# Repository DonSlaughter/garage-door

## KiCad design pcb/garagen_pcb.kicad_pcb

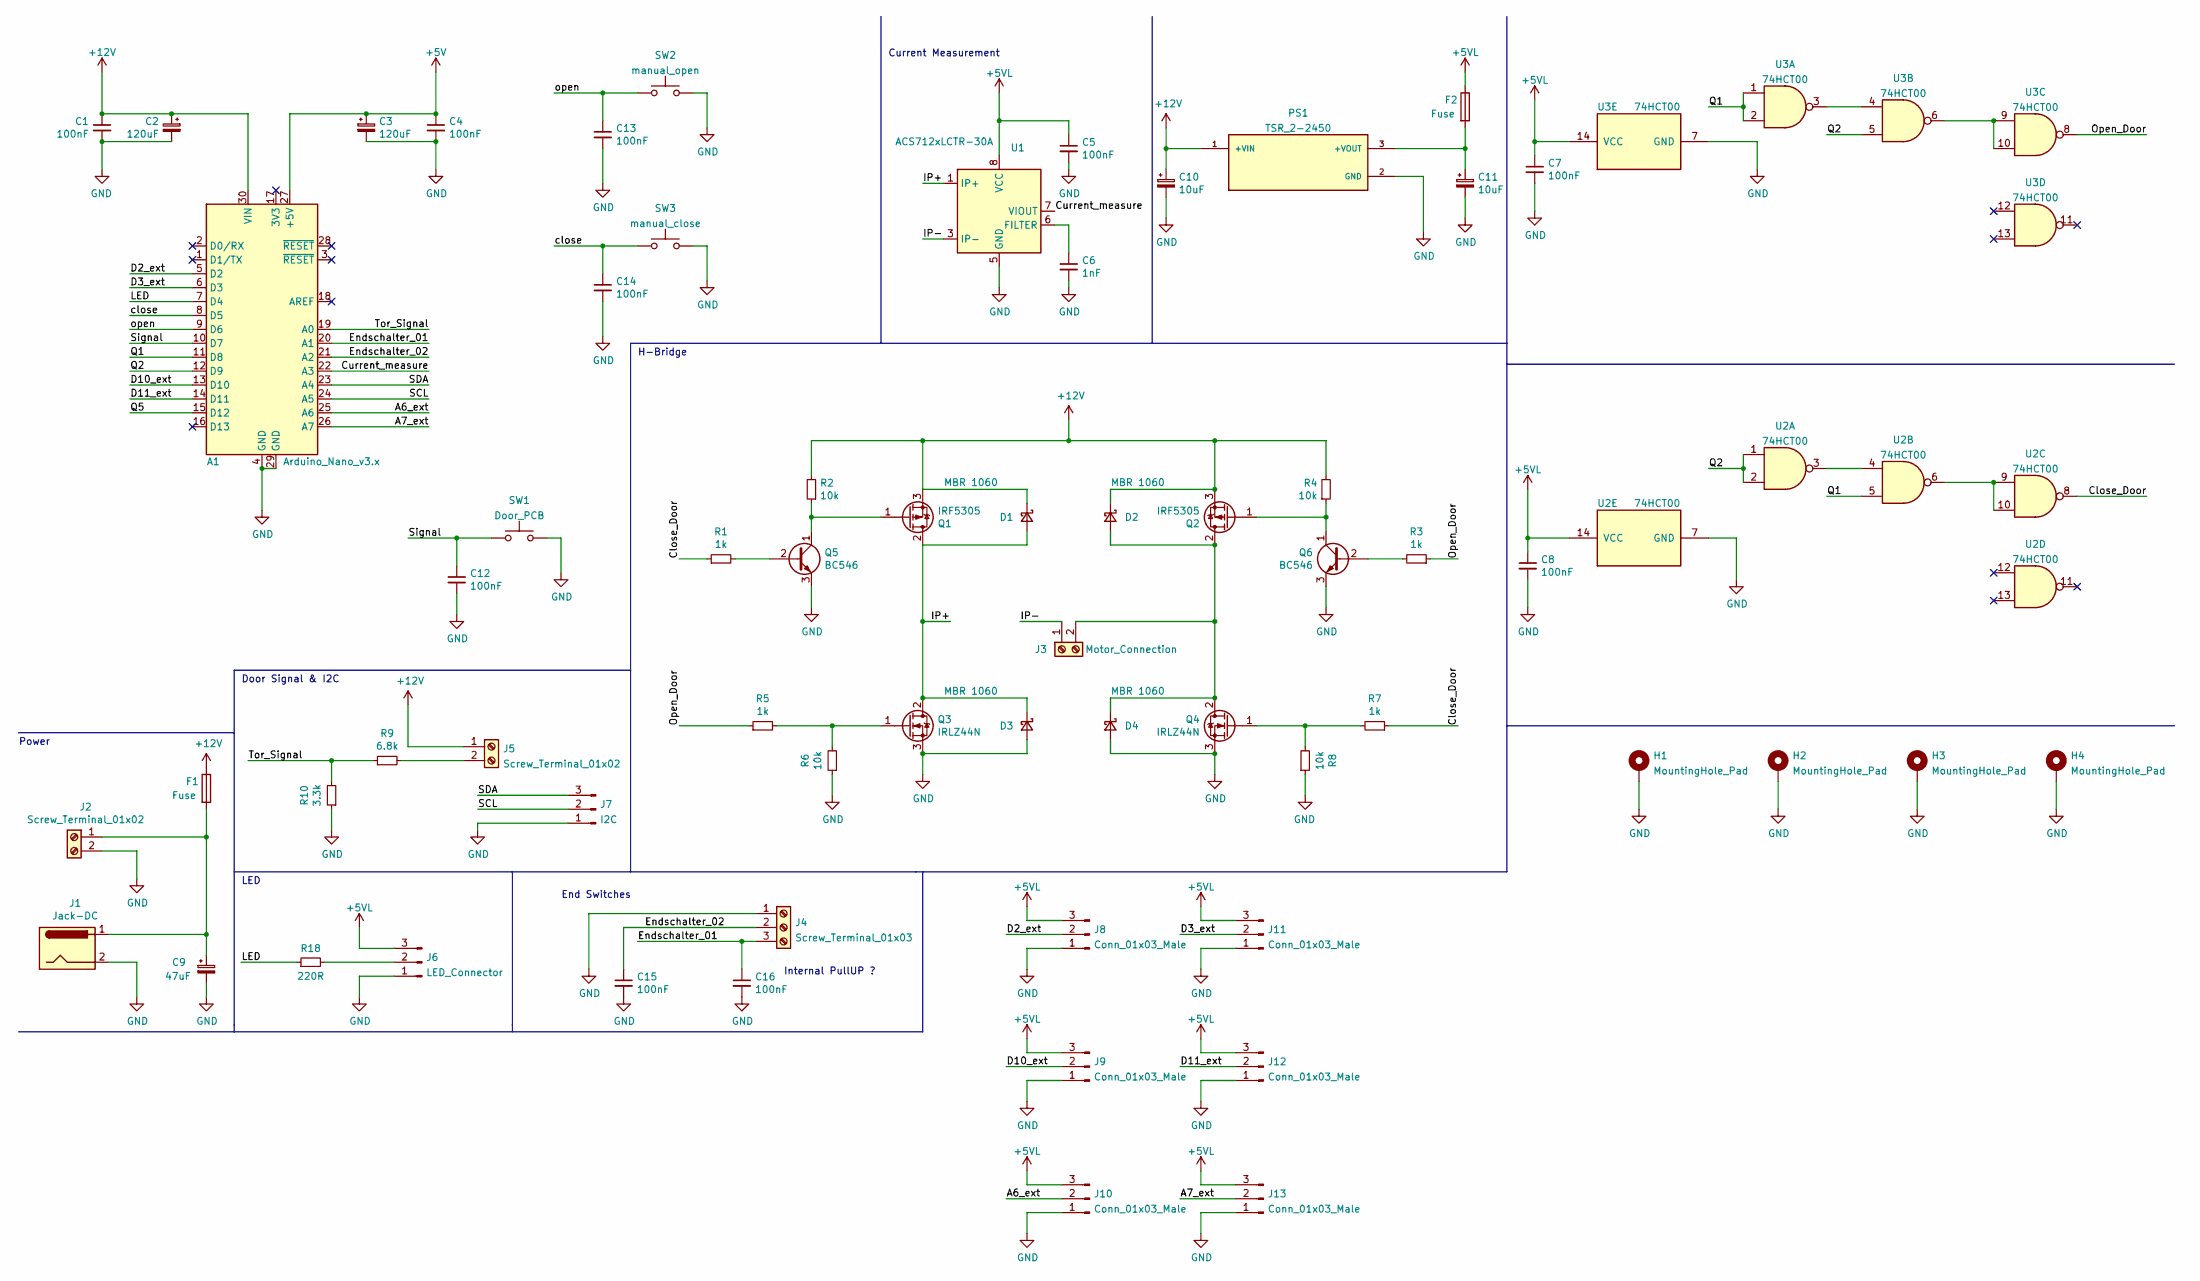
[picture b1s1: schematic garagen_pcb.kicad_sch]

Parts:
A1: Arduino_Nano_v3.x; Arduino_Nano
C1, C4, C5, C7, C8, C12, C13, C14, C15, C16: 100nF; C_Disc_D3.8mm_W2.6mm_P2.50mm
C2, C3: 120uF; CP_Radial_D6.3mm_P2.50mm
C6: 1nF; C_Disc_D3.8mm_W2.6mm_P2.50mm
C9: 47uF; CP_Radial_D6.3mm_P2.50mm
C10, C11: 10uF; CP_Radial_D6.3mm_P2.50mm
D1, D2, D3, D4: MBR 1060; TO-220-2_Vertical
F1, F2: Fuse; Fuseholder_Cylinder-5x20mm_Schurter_0031_8201_Horizontal_Op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
H1, H2, H3, H4: MountingHole_Pad; MountingHole_3.7mm_Pad_Via
J1: Jack-DC; BarrelJack_Horizontal
J2, J5: Screw_Terminal_01x02; TerminalBlock_Phoenix_PT-1,5-2-5.0-H_1x02_P5.00mm_Horizontal
J3: Motor_Connection; TerminalBlock_Phoenix_PT-1,5-2-5.0-H_1x02_P5.00mm_Horizontal
J4: Screw_Terminal_01x03; TerminalBlock_Phoenix_PT-1,5-3-5.0-H_1x03_P5.00mm_Horizontal
J6: LED_Connector; JST_XA_B03B-XASK-1_1x03_P2.50mm_Vertical
J7: I2C; JST_XA_B03B-XASK-1_1x03_P2.50mm_Vertical
J8, J9, J10, J11, J12, J13: Conn_01x03_Male; PinHeader_1x03_P2.54mm_Vertical
PS1: TSR_2-2450; CONV_TSR_2-2450; PARTREV May 14, 2020
Q1, Q2: IRF5305; TO-220-3_Vertical
Q3, Q4: IRLZ44N; TO-220-3_Vertical
Q5, Q6: BC546; TO-92_Inline
R1, R3, R5, R7: 1k; R_Axial_DIN0207_L6.3mm_D2.5mm_P10.16mm_Horizontal
R2, R4, R6, R8: 10k; R_Axial_DIN0207_L6.3mm_D2.5mm_P10.16mm_Horizontal
R9: 6.8k; R_Axial_DIN0207_L6.3mm_D2.5mm_P10.16mm_Horizontal
R10: 3.3k; R_Axial_DIN0207_L6.3mm_D2.5mm_P10.16mm_Horizontal
R18: 220R; R_Axial_DIN0207_L6.3mm_D2.5mm_P10.16mm_Horizontal
SW1: Door_PCB; SW_PUSH_6mm_H4.3mm
SW2: manual_open; SW_PUSH_6mm_H4.3mm
SW3: manual_close; SW_PUSH_6mm_H4.3mm
U1: ACS712xLCTR-30A; SOIC-8_3.9x4.9mm_P1.27mm
U2, U3: 74HCT00; DIP-14_W7.62mm_Socket

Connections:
+5V: A1.27 (+5V), C3.1, C4.1
+5VL: C5.1, C7.1, C8.1, F2.1, J6.3, J8.3, J9.3, J10.3, J11.3, J12.3, J13.3, U1.8 (VCC), U2.14 (VCC), U3.14 (VCC)
+12V: A1.30 (VIN), C1.1, C2.1, C10.1, D1.1 (K), D2.1 (K), F1.1, J5.1, PS1.1 (+VIN), Q1.3 (S), Q2.3 (S), R2.2, R4.2
/A6_ext: A1.25 (A6), J10.2
/A7_ext: A1.26 (A7), J13.2
/Close_Door: R1.1, R7.1, U2.8
/Current_measure: A1.22 (A3), U1.7 (VIOUT)
/D2_ext: A1.5 (D2), J8.2
/D3_ext: A1.6 (D3), J11.2
/D10_ext: A1.13 (D10), J9.2
/D11_ext: A1.14 (D11), J12.2
/Endschalter_01: A1.20 (A1), C16.1, J4.3
/Endschalter_02: A1.21 (A2), C15.1, J4.2
/IP+: D1.2 (A), D3.1 (K), Q1.2 (D), Q3.2 (D), U1.1 (IP+), U1.2 (IP+)
/IP-: J3.1, U1.3 (IP-), U1.4 (IP-)
/LED: A1.7 (D4), R18.1
/Open_Door: R3.1, R5.1, U3.8
/Q1: A1.11 (D8), U2.5, U3.1, U3.2
/Q2: A1.12 (D9), U2.1, U2.2, U3.5
/Q5: A1.15 (D12)
/SCL: A1.24 (A5), J7.2
/SDA: A1.23 (A4), J7.3
/Signal: A1.10 (D7), C12.1, SW1.1
/Tor_Signal: A1.19 (A0), R9.1, R10.2
/close: A1.8 (D5), C14.1, SW3.1
/open: A1.9 (D6), C13.1, SW2.1
GND: A1.4 (GND), A1.29 (GND), C1.2, C2.2, C3.2, C4.2, C5.2, C6.2, C7.2, C8.2, C9.2, C10.2, C11.2, C12.2, C13.2, C14.2, C15.2, C16.2, D3.2 (A), D4.2 (A), H1.1, H2.1, H3.1, H4.1, J1.2, J2.2, J4.1, J6.1, J7.1, J8.1, J9.1, J10.1, J11.1, J12.1, J13.1, PS1.2 (GND), Q3.3 (S), Q4.3 (S), Q5.3 (E), Q6.3 (E), R6.1, R8.1, R10.1, SW1.2, SW2.2, SW3.2, U1.5 (GND), U2.7 (GND), U3.7 (GND)
unnamed: C6.1, U1.6 (FILTER)
unnamed: C9.1, F1.2, J1.1, J2.1
unnamed: C11.1, F2.2, PS1.3 (+VOUT)
unnamed: D2.2 (A), D4.1 (K), J3.2, Q2.2 (D), Q4.2 (D)
unnamed: J5.2, R9.2
unnamed: J6.2, R18.2
unnamed: Q1.1 (G), Q5.1 (C), R2.1
unnamed: Q2.1 (G), Q6.1 (C), R4.1
unnamed: Q3.1 (G), R5.2, R6.2
unnamed: Q4.1 (G), R7.2, R8.2
unnamed: Q5.2 (B), R1.2
unnamed: Q6.2 (B), R3.2
unnamed: U2.3, U2.4
unnamed: U2.6, U2.9, U2.10
unnamed: U3.3, U3.4
unnamed: U3.6, U3.9, U3.10

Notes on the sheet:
Current Measurement
Power
Door Signal & I2C
Internal PullUP ?
End Switches
H-Bridge
LED

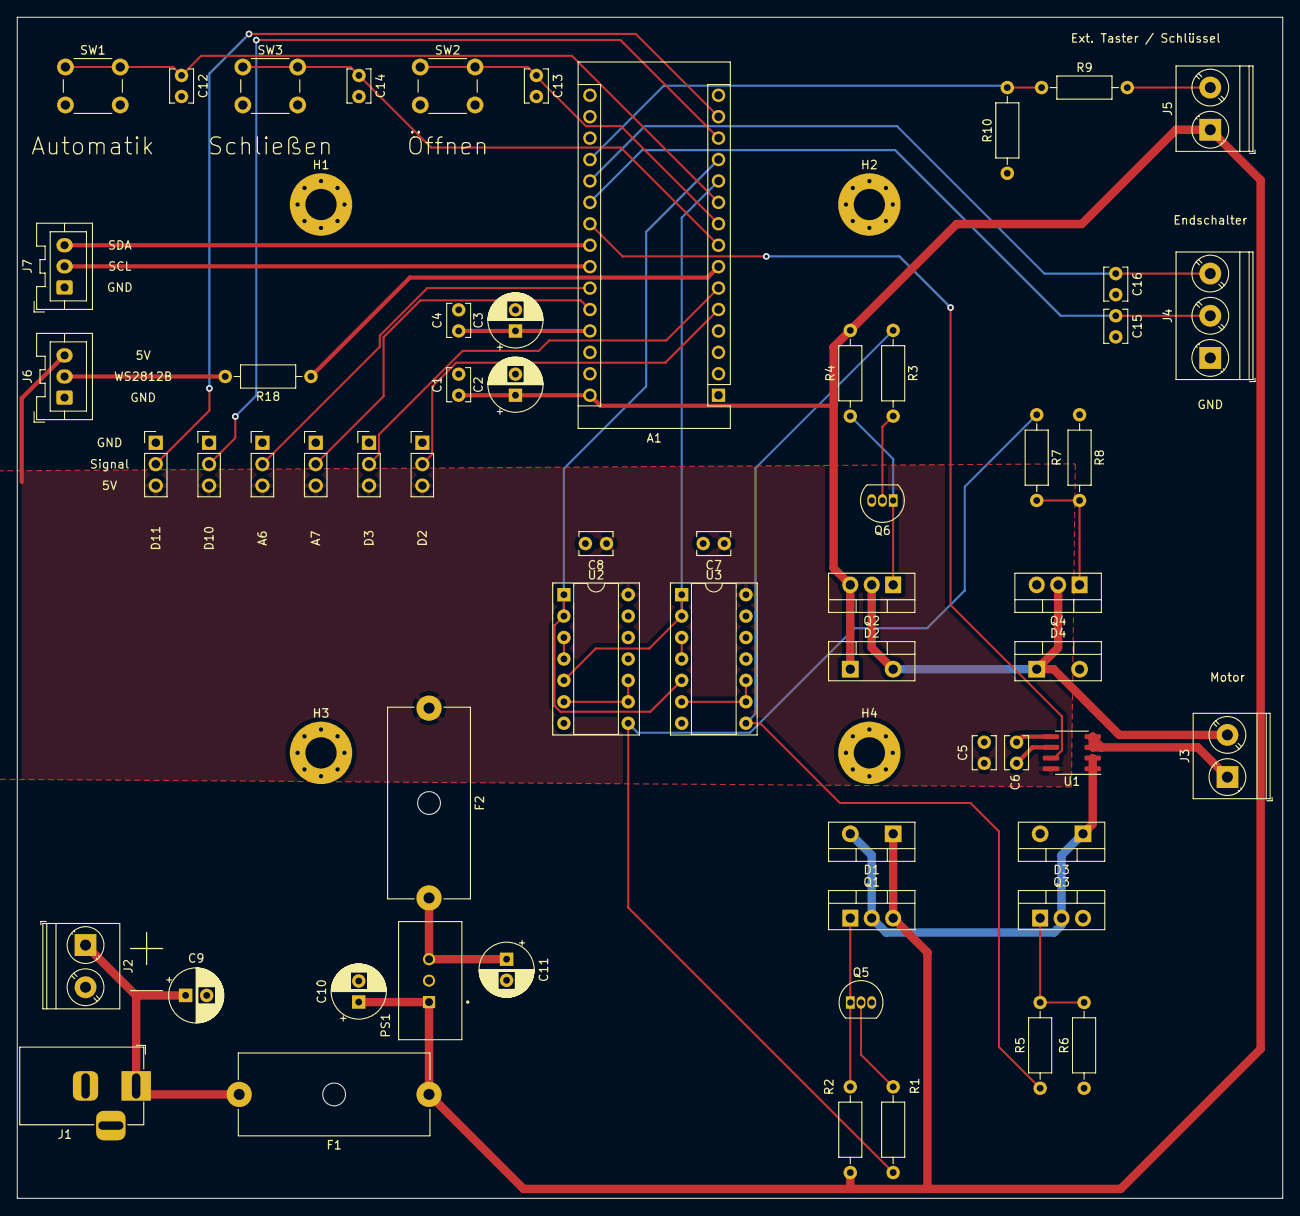
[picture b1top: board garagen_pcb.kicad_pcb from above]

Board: 2 copper layers, 150.0 x 140.0 mm, 64 parts (0 on the bottom side), 42 nets.

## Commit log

2022-02-11 breadboard test
2022-02-19 rundamential working stuff
2022-03-06 test
2022-03-06 first test
2022-03-08 fore works
2022-03-08 gitignore
2022-03-10 first working stuff
2022-03-10 smaller functions
2022-03-11 class test
2022-03-11 don't allow illegal motor state in any case
    given the case:
    motor_start_down()
    ...
    motor_start_up()
    will set both pins high for a 'little' while.
2022-03-11 Always intialize all members!
2022-03-11 Introduce "Events"
2022-03-11 create list of switches
2022-03-11 Revert "create list of switches"
    that was stupid
    This reverts commit 9bc6b53b82e797457260ee573af553c166521f08.
2022-03-11 use a list of switches
2022-03-13 rename functions
2022-03-13 removed dumb file d in root
2022-03-13 emergency buttons realised as button class
2022-03-13 gitignore changed to ignore cache
2022-03-13 comments added
2022-03-13 sate comments
2022-03-13 button class with debounce delay constructor
2022-03-13 manual buttons working correctly
2022-03-13 working condition
2022-03-14 gitignore stuff
2022-03-14 leds test
2022-03-14 suspend implemented
2022-03-14 new states for open and close positions
2022-03-14 broken
2022-03-14 working
2022-03-15 led status
2022-03-15 enums and state to main.h
2022-03-16 not working timeoff -.-
2022-03-16 .cache deleted and timer changes
2023-08-12 new .gitignore
2023-08-12 removed chache
2023-08-12 compl
2023-08-12 complc removed
2023-08-12 stuff
2023-08-12 working door
